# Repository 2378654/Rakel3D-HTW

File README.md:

# Rakel3D

This project simulates the **squeegee technique** using a real squeegee (drawing instrument) on a real wall.

The painting is projected onto the wall using a **projector**.

The project is based on a **multi-layer color model** taken from a previous project by [Brzoska(2023)](https://github.com/donatbrzoska/Layers).

---

## Requirements

### Software
- **Unity3D**
  - Version used: `2022.3.8f1`

### SteamVR Startup Instructions
1. Start SteamVR and wait until **all four base stations** are connected.
2. Turn on the trackers in the following order:
   1. Upper tracker (above the power bank)
   2. Lower tracker

> ⚠️ If devices are paired in a different order, the device numbers of the **“Top”** and **“Bottom”** GameObjects may need to be adjusted.

### Lighthouse Tracking
- Four [Lighthouses (Base Stations 2.0)](https://www.vive.com/de/accessory/base-station2/)
- One of the following headsets:
  - [Vive Pro](https://www.vive.com/de/product/vive-pro2/overview/)
  - **Vive Cosmos Elite**

> **Note:**  
> The headset is **not worn**, but required to establish the Lighthouse Tracking connection.

### Calibration
- SteamVR room setup is used for system calibration.

### Rakel (Squeegee) Controller
- Homemade controller consisting of:
  - Two [Vive Trackers 3.0](https://www.vive.com/de/accessory/tracker3/)
  - Power bank for power supply
  - ESP32 microcontroller with input elements
  - Modified squeegee with a soft edge to protect the wall

### Connectivity
- **Dongle**
- ESP32 connected via **USB** to forward data to Unity
---

## Project Control

### Switching Between Controllers
- Select the **“Interaction”** GameObject
- Toggle the checkbox to activate or deactivate the wall controller

---

### Adjusting the Virtual Squeegee Edge
- Select the **“LineRenderer”** GameObject
- Adjust the following parameters:
  - `Offset X / Y`
  - `Mult X / Y`

---

### Adjusting the Distance to the Wall
- Select the **“DistanceController”** GameObject
- Adjust the **Canvas Offset**

---

## Operation

The operation differs depending on the controller being used.

---

### Squeegee Controller
(All settings are made directly on the squeegee controller)

- Adjust canvas size or squeegee parameters using sliders:
  - **Squeegee Length (Width)**
  - **Amount of Paint (Height)**
- Confirm canvas size and refill squeegee using:
  - `Refill (Done)`
- Color selection via rotary potentiometer:
  - `Color`
- Undo last stroke:
  - `Undo`
- Empty squeegee:
  - `Clear Squeegee`
- Clear canvas:
  - `Clear Canvas`
- Save images:
  - `Save 1`, `Save 2`, `Save 3`
- Load images:
  - `Load 1`, `Load 2`, `Load 3`
- Toggle blur mode:
  - `Light Mixing` (light / heavy)
- Pressure is detected via **two pressure sensors**

---

### Wall Controller
(All settings are made on the wall UI)

- Adjust canvas size:
  - `Height + / -`
  - `Width + / -`
- Open full UI:
  - `UI`
- Color selection:
  - 23 individual color buttons
- Undo last stroke:
  - `Undo`
- Toggle blur mode:
  - `Light Mixing`
- Empty squeegee:
  - `Clear Squeegee`
- Clear canvas:
  - `Clear Canvas`
- Adjust squeegee parameters:
  - `Squeegee Length`
  - `Amount of Paint`
- Adjust pressure:
  - `Pressure + / -`
- Switch modes:
  - `Save and Load / Colors`
- Scroll through colors:
  - `^` and `v`

---

## Troubleshooting

- If the virtual representation shows **jerky movements**, reflective surfaces may interfere with tracking.
- Make sure **all reflective surfaces are covered**.

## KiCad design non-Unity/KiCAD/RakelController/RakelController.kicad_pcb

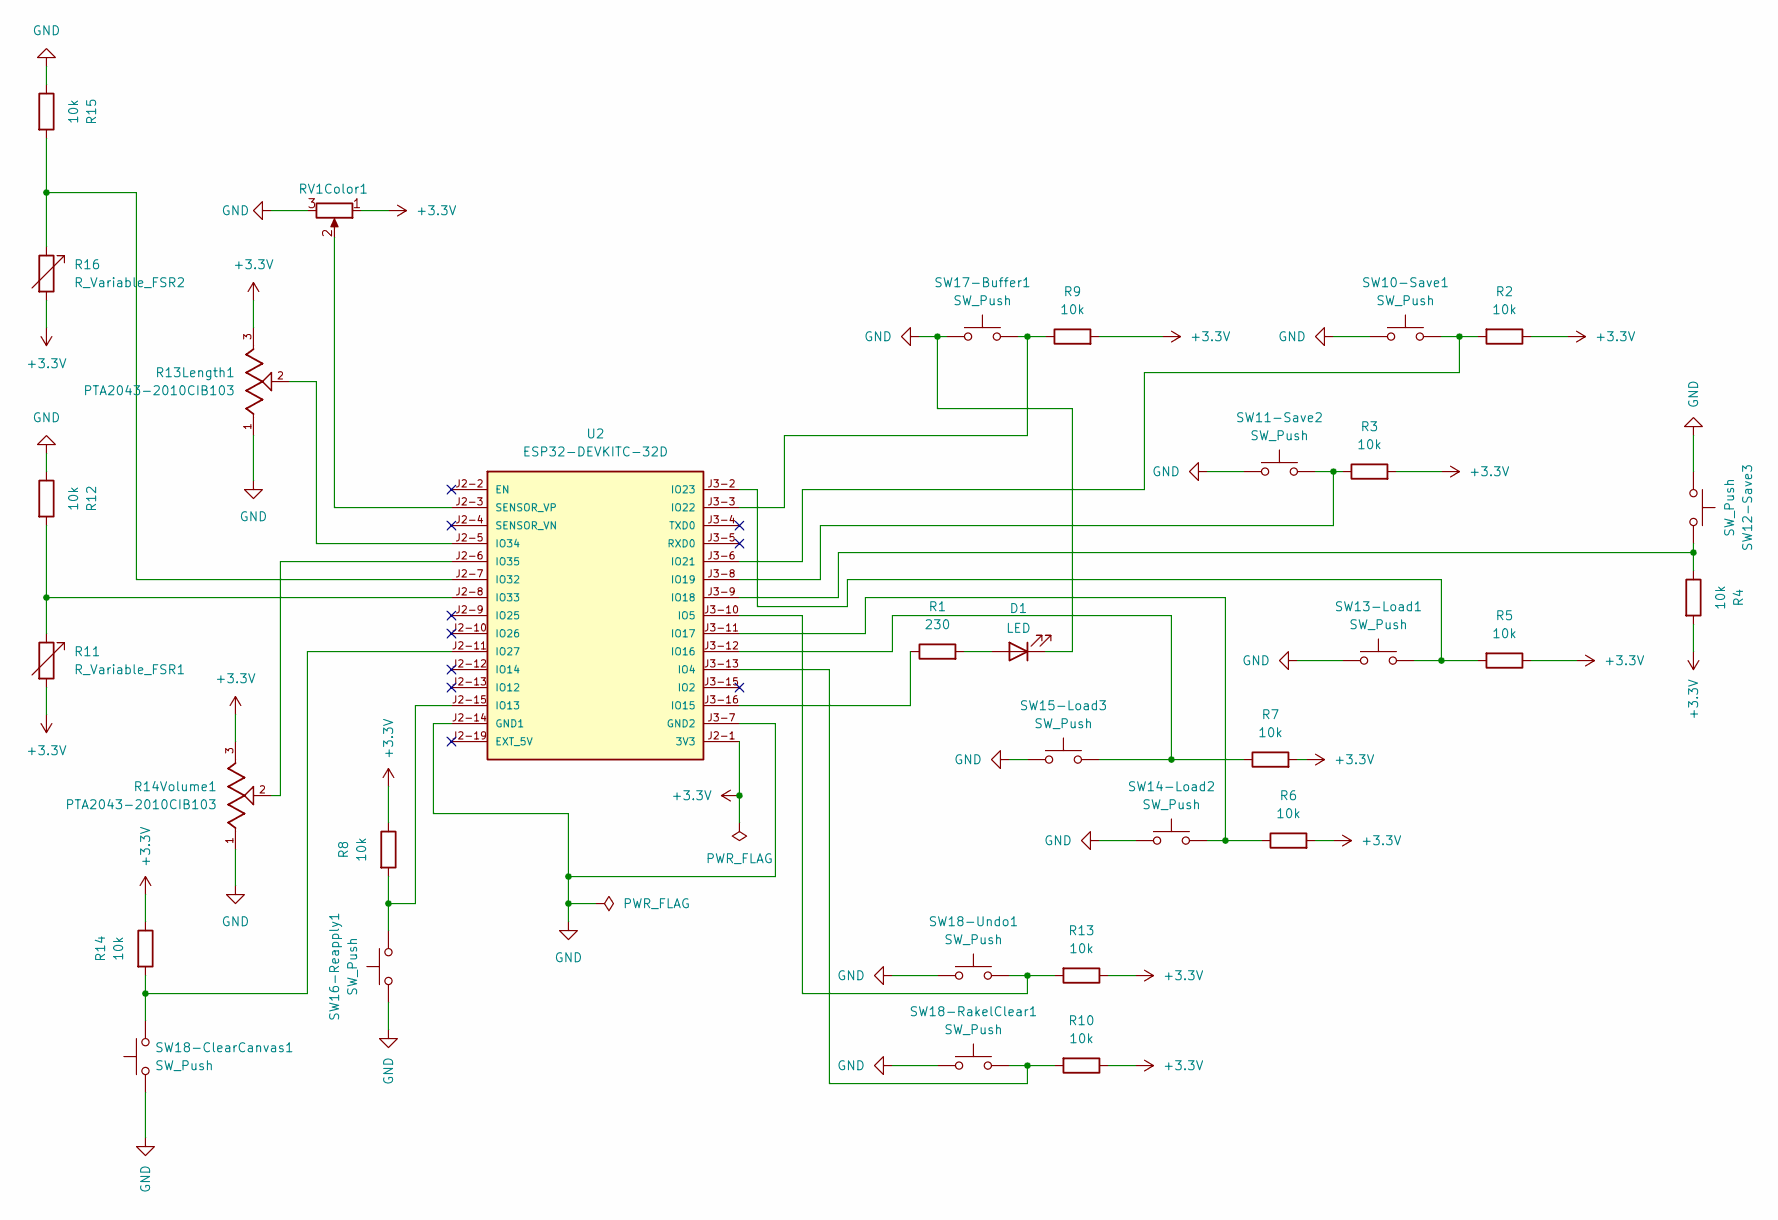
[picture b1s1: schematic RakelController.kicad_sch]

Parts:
D1: LED; LED_D5.0mm
R1: 230; R_Axial_DIN0207_L6.3mm_D2.5mm_P7.62mm_Horizontal
R2, R3, R4, R5, R6, R7, R8, R9, R10, R12, R13, R14, R15: 10k; R_Axial_DIN0207_L6.3mm_D2.5mm_P7.62mm_Horizontal
R11: R_Variable_FSR1; R_Axial_DIN0207_L6.3mm_D2.5mm_P7.62mm_Horizontal
R13Length1, R14Volume1: PTA2043-2010CIB103; Potentiometer_Bourns_PTA2043_Single_Slide; PARTREV 04/21
R16: R_Variable_FSR2; R_Axial_DIN0207_L6.3mm_D2.5mm_P7.62mm_Horizontal
RV1Color1: R_Potentiometer; Potentiometer_Alps_RK09K_Single_Vertical
SW10-Save1, SW11-Save2, SW12-Save3, SW13-Load1, SW14-Load2, SW15-Load3, SW16-Reapply1, SW17-Buffer1, SW18-ClearCanvas1, SW18-RakelClear1, SW18-Undo1: SW_Push; SW_PUSH-12mm
U2: ESP32-DEVKITC-32D; MODULE_ESP32-DEVKITC-32D; PARTREV V4

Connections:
+3.3V: R2.1, R3.2, R4.2, R5.1, R6.2, R7.2, R8.1, R9.2, R10.1, R11.2, R13.1, R13Length1.3, R14.1, R14Volume1.3, R16.2, RV1Color1.1, U2.J2-1 (3V3)
GND: D1.1 (K), R12.1, R13Length1.1, R14Volume1.1, R15.1, RV1Color1.3, SW10-Save1.1, SW11-Save2.1, SW12-Save3.1, SW13-Load1.1, SW14-Load2.1, SW15-Load3.1, SW16-Reapply1.1, SW17-Buffer1.1, SW18-ClearCanvas1.1, SW18-RakelClear1.1, SW18-Undo1.1, U2.J2-14 (GND1), U2.J3-7 (GND2)
unnamed: D1.2 (A), R1.2
unnamed: R10.2, SW18-RakelClear1.2, U2.J3-13 (IO4)
unnamed: R13.2, SW18-Undo1.2, U2.J3-10 (IO5)
unnamed: R8.2, SW16-Reapply1.2, U2.J2-15 (IO13)
unnamed: R1.1, U2.J3-16 (IO15)
unnamed: R7.1, SW15-Load3.2, U2.J3-12 (IO16)
unnamed: R6.1, SW14-Load2.2, U2.J3-11 (IO17)
unnamed: R4.1, SW12-Save3.2, U2.J3-9 (IO18)
unnamed: R3.1, SW11-Save2.2, U2.J3-8 (IO19)
unnamed: R2.2, SW10-Save1.2, U2.J3-6 (IO21)
unnamed: R9.1, SW17-Buffer1.2, U2.J3-3 (IO22)
unnamed: R5.2, SW13-Load1.2, U2.J3-2 (IO23)
unnamed: R14.2, SW18-ClearCanvas1.2, U2.J2-11 (IO27)
unnamed: R15.2, R16.1, U2.J2-7 (IO32)
unnamed: R11.1, R12.2, U2.J2-8 (IO33)
unnamed: R13Length1.2, U2.J2-5 (IO34)
unnamed: R14Volume1.2, U2.J2-6 (IO35)
unnamed: RV1Color1.2, U2.J2-3 (SENSOR_VP)

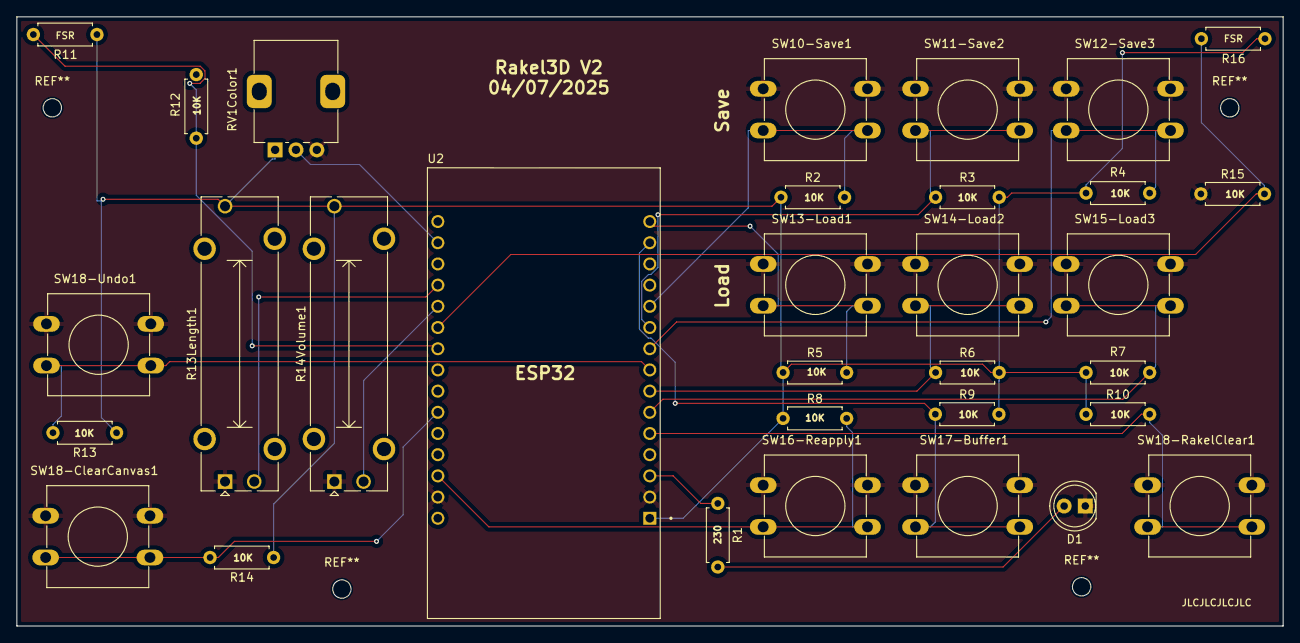
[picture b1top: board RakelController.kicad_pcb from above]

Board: 2 copper layers, 151.8 x 73.0 mm, 32 parts (0 on the bottom side), 20 nets.

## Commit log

2024-08-14 Added gitignore for unity
2024-08-15 first version with real rakel
2024-08-20 New Parameters
2024-08-26 First Implementation for Rotation
2024-08-26 First Tilt Implementation
2024-09-09 all 3 Rakel Length as Comment in Cofiguration.cs + Rotation and Tilt Implementation start
2024-09-10 Update README.md added ToDos
2024-09-10 Update README.md, fixed Formatting
2024-09-10 Update README.md, Feedback to Project Demonstration and other information
2024-09-16 ÃAdded LineRenderer as Representation of current Rakel Position
2024-09-17 Added RakelLineRenderer as 2D Representation
2024-10-01 Last To Dos added
2024-10-05 Added Comments, Parameters set for VR-SetUp at School
2024-10-05 Added Comments
2024-10-05 Changed Device Index for RenderedRakel to 7 and Wall to 8
2024-12-19 updated gitignore
2025-02-22 added Color Selection, Saves, Tabs on Wall
2025-02-22 added all colors with labels
2025-02-27 fixed rotation for real rakel
2025-02-27 Removed RotaionValue Obj. because it isnt needed
2025-02-27 increase Rakel CellVolume to 10 Canvas, CellVolume to 3, Colume to 600
2025-02-28 added todos
2025-03-02 Edit README.md
2025-04-04 added Pressure, Texts for every Save Button, Tilt, TabSwitch Button, lowered all component on the wall
2025-04-04 final commit, nothing new
2025-04-05 removed unnecessary comments, added comment
2025-04-05 Deactivated Testobject
2025-04-20 first Notes for master
2025-04-21 Added new UI. WIP error when scrolling down
2025-04-21 Fixed Scroll Bug
2025-05-10 POC Rakelcontroller, currently only wired possible
2025-05-10 Add new file
2025-05-10 Added Arduino Code
2025-05-19 added new Arduino file, fixed some bugs
2025-06-26 Changed current ReadMe to Notes. Added New ReadMe
2025-06-26 Added images folder for ReadMe Help
2025-07-05 Added new UI, WIP TrackerStrokeState isnt working correctly StrokeBegin needs to be called only at start of stroke
2025-07-05 Added canvassize, undo, canvas clear
2025-07-08 Changes TrackerStrokeState.cs. Currently lagging sometimes (wip). Pressure isnt shown on wall
2025-07-08 added both mac addresses as comment
2025-07-08 Added Screenshot feature. TODO: Add adjustable size. WIP: Currently screenshot with sort of lensflare on canvas
2025-07-09 Added multX, multY, offsetX and offsetY from LineRenderer to TrackerRakelPositionX.cs, TrackerRakelPositionY.cs. Saving works. TODO still lensflare from Light visible
2025-07-11 Fixed and Added Buttons to Wall-System.
2025-07-11 Added Checkbox if Buttons on Wall are used or RakelController --> Changes the way the when the Rakel paints
2025-07-15 Changed material to save Screenshots. Tested for support of the final controller inputs (new: Undo, Clear canvas and adjustable canvas size) Adjusted Resolution from 40 to 25 to increase performance
2025-07-15 Added updated Arduino Code. Adjustable canvas on every programmstart
2025-07-17 Added Undo and CanvasClear Buttons for Wallcontroller. TODO: fixing bug in ApplyRakelSettings when picking color. When ClearingCanvas, selecting a color doesnt work anymore.
2025-07-18 Clear Rakel working. Volume has an Indicator. Box colliders adjusted again. Undo working but TODO: Undo on wall doesnt work cause touching the canvas creates a new stroke no matter if you touch the c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
2025-07-19 0 to false, 1 to true for sizeDone
2025-07-21 changed sizeDone location from CanvasClear to Reapply(Refill)
2025-07-22 Added Confirmation to clear the Canvas. Sliderposition on wall are now dynamic. ApplySize fully implemented. TODO: implement counter to calculate the amount of used Settings for evaluation. TODO: Fix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
2025-07-23 Fixed Saving. PNGs now contain the whole painting. TODO: Fix Undo for Wallcontroller. Implement Settingscounter for evaluation.
2025-07-23 Added SettingsCounter to evaluate the used Settings per testperson. Undo is working on wallcontroller. Bug fixed that you were able to draw if the ui was active.
2025-07-23 TODO: Adjusting Boxcolliders for Wallcontroller. TODO: Check for material without reflection TODO: Check if theres a fix to stop potentiometer from changing colors if between them
2025-07-25 Fixed Bug: Painting when using WallController.
2025-07-25 Adjusted Collider Size for Buttons for current Tracking
2025-07-25 added structure for Autodesk and KiCAD
2025-07-28 changed paths for non unity files. created non unity folder
2025-07-28 Added RakelController Lit as 3mf File for Autodesk
2025-07-28 Added RakelController Case as 3mf file for Autodesk
2025-07-28 removed placeholder
2025-07-28 added KiCAD project
2025-07-29 final esp script
2025-07-29 Adjusted actual painting location and location of the LineRenderer by changing the z-position of the linerenderer
2025-08-06 After Evaluation: changed two textboxes for Wall-Controller. Adjusted Colorweel rotation
2025-08-12 Upload New File
2025-08-18 Fixed the accuracy. Added Textbox if squeegee is refilled.
2025-08-27 adjusted stroke width. Fits better to the width of the linerenderer of the virtual representation
2025-08-29 edited readme
2025-08-30 changed Structure of readme
2025-09-01 added available settings with explanation
2025-09-01 added axplanation for wall controller
2025-09-03 created nodes.md
2025-09-03 Added readme to Rakelcontroller branch
2025-09-03 Add new directory
2025-09-03 removed old files
2026-01-14 added *.log to gitignore
